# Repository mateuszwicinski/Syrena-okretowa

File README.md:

# Syrena-okretowa
Projekt wykonany w ramach laboratorium na Politechnice Gdańskiej.

**Opis projektu**
Zadanie polegało na zaprojektowaniu od podstaw schematu ideowego oraz dwustronnego obwodu drukowanego (PCB) dla generatora sygnału dźwiękowego (syreny okrętowej). Sercem układu jest popularny timer NE555, współpracujący z układem wzmacniającym opartym na tranzystorach bipolarnych, który wysterowuje głośnik. 

**Spis plików i ich zawartość**
* **Wiciński.sch** – Schemat ideowy syreny okrętowej.
* **Wiciński.brd** – Projekt obwodu drukowanego.

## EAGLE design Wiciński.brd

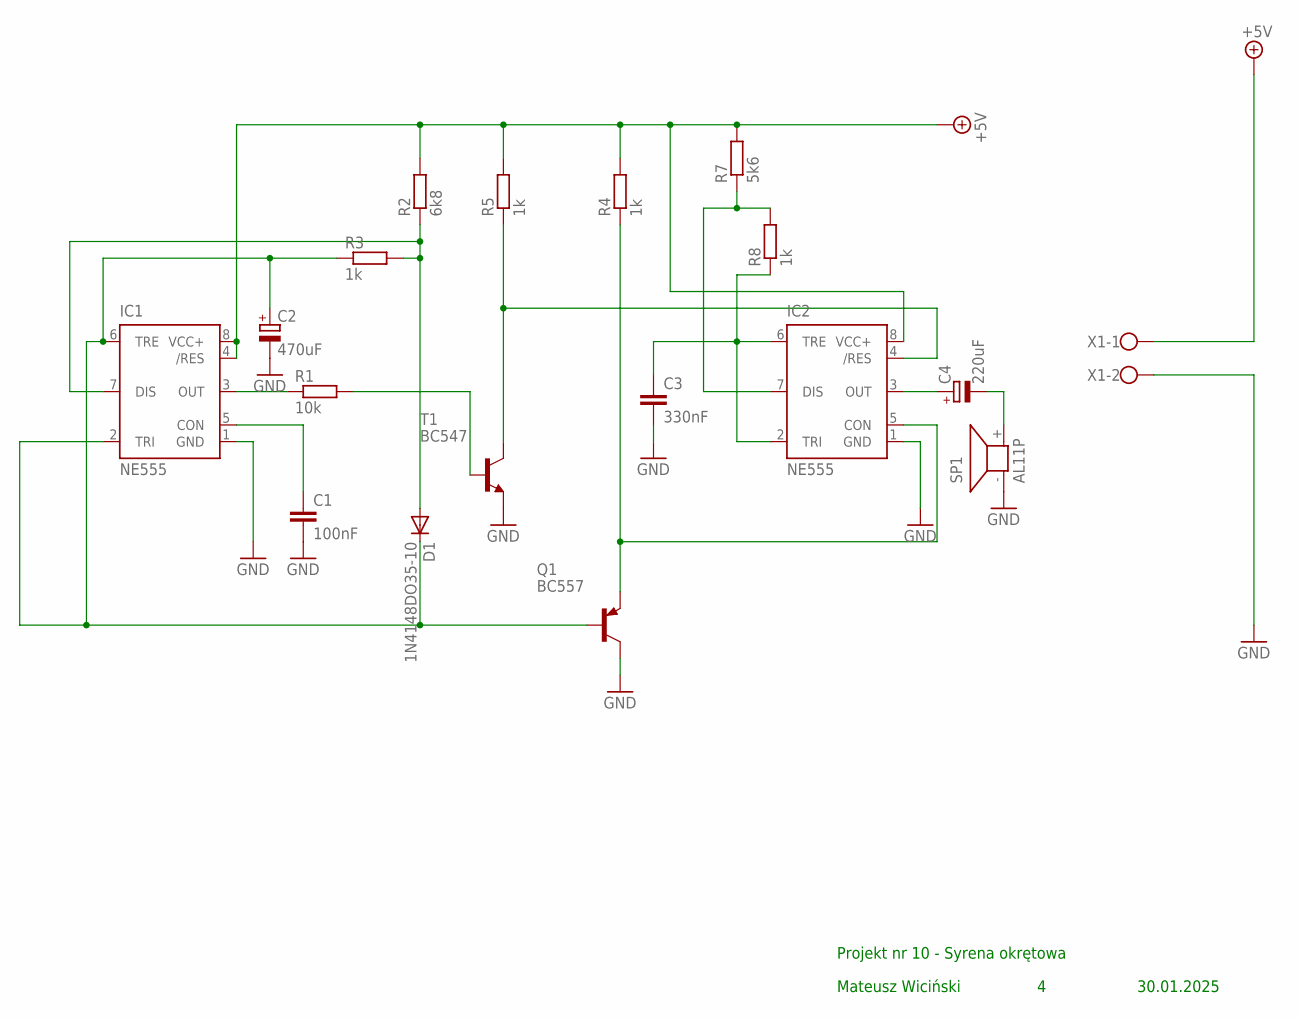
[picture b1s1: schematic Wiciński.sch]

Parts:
C1: 100nF; C050-050X075
C2: 470uF; 140CLH-1014
C3: 330nF; C050-050X075
C4: 220uF; 140CLH-1014
D1: 1N4148DO35-10; DO35-10
IC1, IC2: NE555; DIL-08
Q1: BC557; TO92
R1: 10k; 0207/10
R2: 6k8; 0207/10
R3, R4, R5, R8: 1k; 0207/10
R7: 5k6; 0207/10
SP1: AL11P
T1: BC547; TO92
X1: W237-102

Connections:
+5V: IC1.4 (/RES), IC1.8 (VCC+), IC2.8 (VCC+), R2.2, R4.2, R5.2, R7.2, X1.1
GND: C1.2, C2.-, C3.2, IC1.1 (GND), IC2.1 (GND), Q1.3 (C), SP1.- (1), T1.1 (E), X1.2
unnamed: IC1.3 (OUT), R1.1
unnamed: C2.+, D1.C, IC1.2 (TRI), IC1.6 (TRE), Q1.2 (B), R3.1
unnamed: C1.1, IC1.5 (CON)
unnamed: D1.A, IC1.7 (DIS), R2.1, R3.2
unnamed: R1.2, T1.2 (B)
unnamed: C4.+, IC2.3 (OUT)
unnamed: IC2.5 (CON), Q1.1 (E), R4.1
unnamed: C4.-, SP1.+ (2)
unnamed: IC2.4 (/RES), R5.1, T1.3 (C)
unnamed: IC2.7 (DIS), R7.1, R8.2
unnamed: C3.1, IC2.2 (TRI), IC2.6 (TRE), R8.1

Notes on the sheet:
Projekt nr 10 - Syrena okrętowa
Mateusz Wiciński
30.01.2025

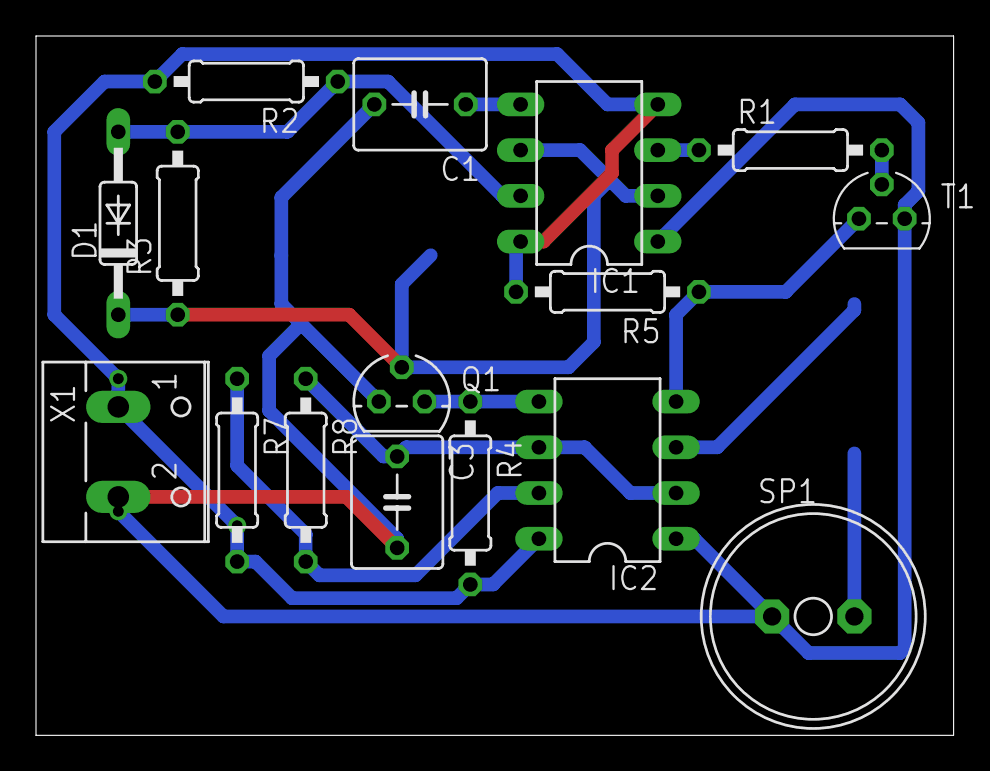
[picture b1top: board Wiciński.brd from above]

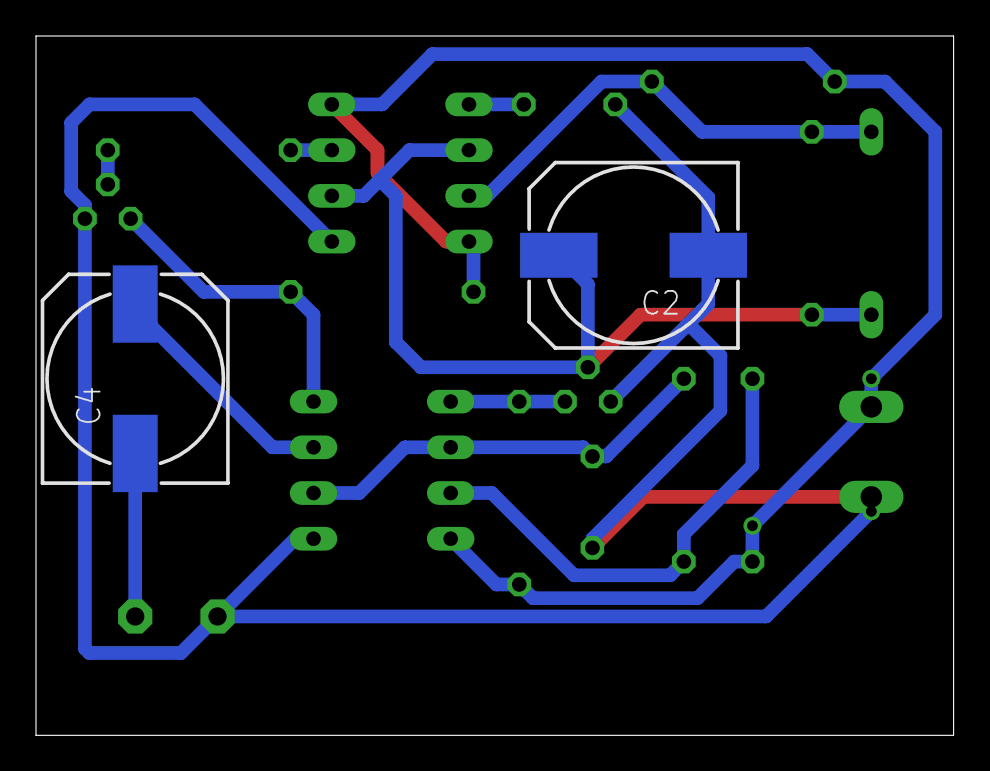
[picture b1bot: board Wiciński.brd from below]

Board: 2 copper layers, 51.0 x 38.9 mm, 18 parts (2 on the bottom side), 13 nets.
